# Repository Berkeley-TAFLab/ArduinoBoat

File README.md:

# Software for TAFLab Arduino Drone

Contributors: Professor Reza Alam, Evan Kuo, Arsh Khan, and Nick Bui

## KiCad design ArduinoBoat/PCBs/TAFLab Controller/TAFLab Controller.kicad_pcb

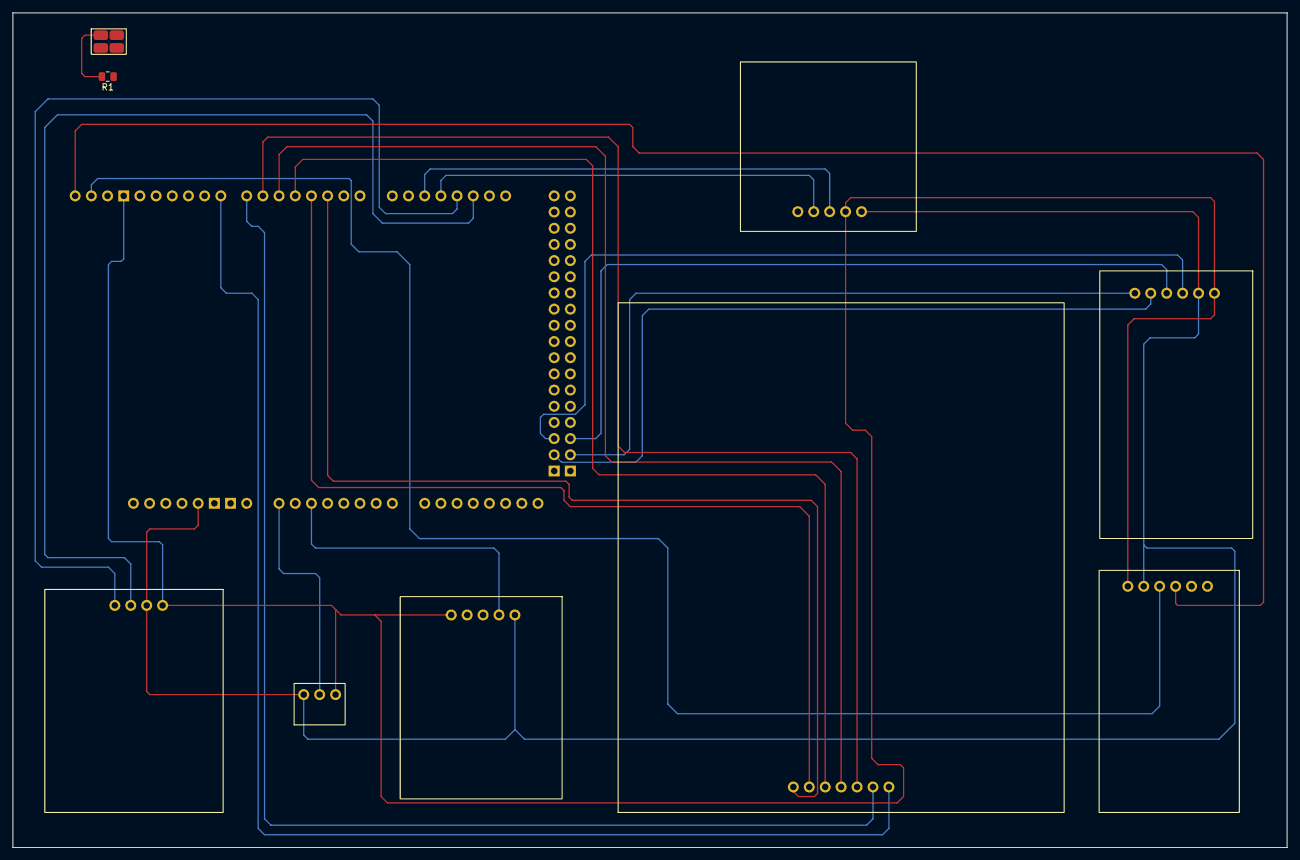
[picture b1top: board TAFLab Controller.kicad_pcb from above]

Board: 2 copper layers, 200.0 x 131.0 mm, 10 parts (0 on the bottom side), 22 nets.

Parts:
A1: Arduino_Mega2560_R3_Shield
R1: 10k; R_0805_2012Metric
RV1: R_Potentiometer; Potentiometer
U1: XBeeBreakout
U2: JoyStick
U3: Keypad
U4: HW84_DS3231_CLK_Module
U5: Micro_SD_Module
U7: GT-U7_GPS
U8: PushButton

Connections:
unnamed: A1.D2 (D2_INT0), U3.1 (ROW1)
unnamed: A1.D3 (D3_INT1), U3.2 (ROW2)
unnamed: A1.D16 (D16/TX2), U7.3 (RXD)
unnamed: A1.D17 (D17/RX2), U7.2 (TXD)
unnamed: A1.D18 (D18/TX1), U1.4 (DIN)
unnamed: A1.D19 (D19/RX1), U1.3 (DOUT)
unnamed: A1.D50 (D50_MISO), U5.3 (MISO)
unnamed: A1.D51 (D51_MOSI), U5.4 (MOSI)
unnamed: A1.D52 (D52_SCK), U5.5 (SCK)
unnamed: A1.D53 (D53_CS), U5.6 (CS)
unnamed: A1.A0, RV1.2
unnamed: A1.5V1 (5V), RV1.1, U1.2 (5V), U2.1 (VCC), U4.5 (VCC), U5.2 (VCC), U7.5 (VCC), U8.2 (VCC)
unnamed: A1.GND1 (GND), R1.1, RV1.3, U1.1 (GND), U2.5 (GND), U4.6 (GND), U5.1 (GND), U7.4 (GND)
unnamed: A1.A2, U2.2 (VERT)
unnamed: A1.D6, U3.5 (COL1)
unnamed: A1.D7, U3.6 (COL2)
unnamed: A1.D8, U3.7 (COL3)
unnamed: A1.D4, U3.3 (ROW3)
unnamed: A1.D5, U3.4 (ROW4)
unnamed: A1.SCL, U4.3 (SCL)
unnamed: A1.SDA, U4.4 (SDA)
unnamed: R1.2, U8.1 (GND)

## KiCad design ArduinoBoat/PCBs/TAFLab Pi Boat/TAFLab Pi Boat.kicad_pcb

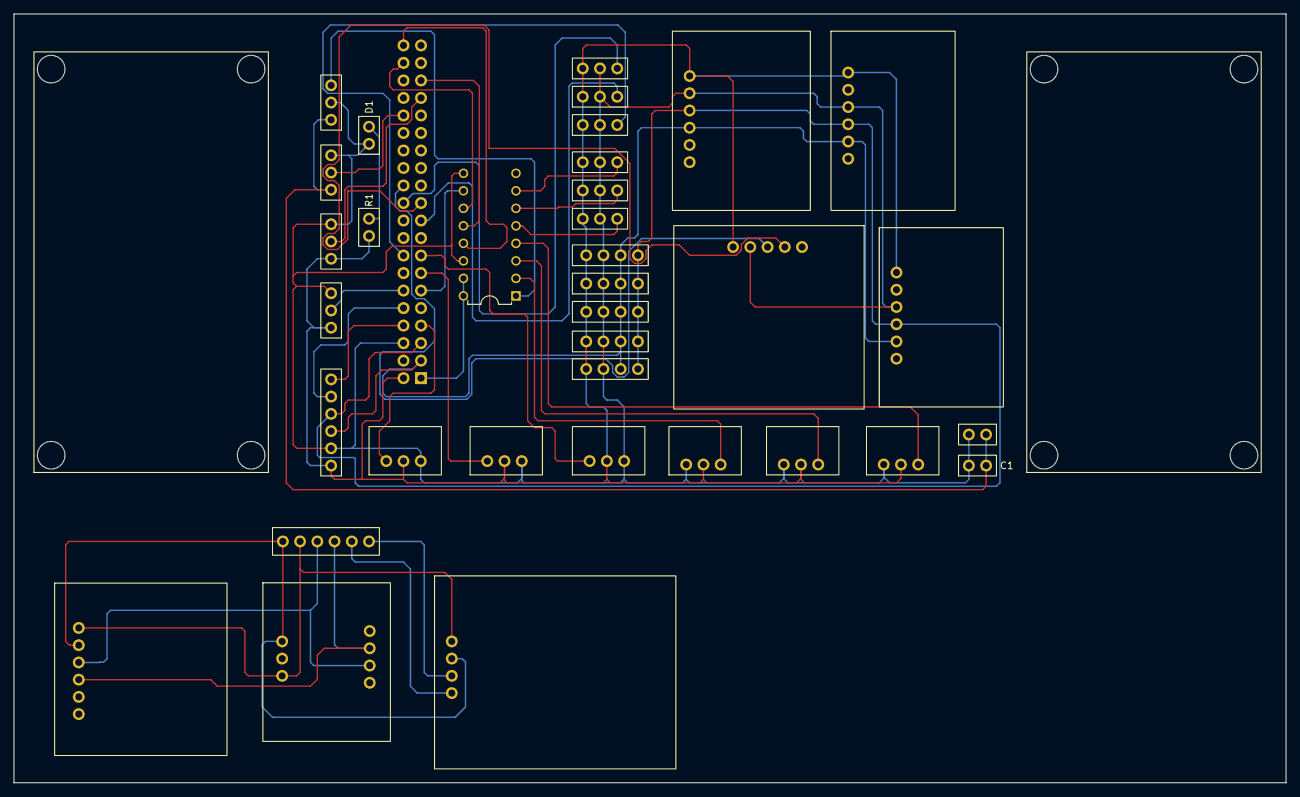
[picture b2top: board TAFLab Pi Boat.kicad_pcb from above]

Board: 2 copper layers, 184.5 x 111.5 mm, 38 parts (0 on the bottom side), 37 nets.

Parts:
C1: 10k µF; Default2Pin
D1: LED; Default2Pin
R1: 300Ω; Default2Pin
RP1: Raspberry_Pi_2_3; RaspberryPi_4
U1: AS5600_Magnetic_Encoder_Windvane
U2: BME280_PHT
U3: XBeeBreakout
U4: GT-U7_GPS
U5: LIS3MDL_Magnetometer
U6: MPU6050_IMU_Accelerometer
U7, U8, U9: DS18B20_Water_Temp_Sensor
U10, U11, U12: HW038_WaterLevelSensor
U13, U15: LM2596S-12; LM2596
U14: INA219_BatteryPowerSensor
U16, U17, U18: ActuatorConnector
U19, U20, U21, U22, U23, U24, U30: Default3Pin
U25, U26, U27, U28, U29: Default4Pin
U31: Top_Boat_PCB
U32: SailWireConnector
U33: MCP3008
U34: Default2Pin

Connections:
+3.3V: RP1.1 (+3.3V_1), U33.15 (Vref), U33.16 (Vdd)
+5V: R1.1, RP1.2 (+5V_1), U4.5 (5V), U5.1 (5V), U6.1 (5V), U7.2 (5V), U8.2 (5V), U9.2 (5V), U10.2 (5V), U11.2 (5V), U12.2 (5V), U14.1 (5V), U16.1 (5V), U17.1 (5V), U19.1 (5V), U20.1 (5V), U21.1 (5V), U22.1 (5V), U23.1 (5V), U24.1 (5V), U25.1 (5V), U26.1 (5V), U27.1 (5V), U28.1 (5V), U29.1 (5V), U32.1 (5V)
+8V: C1.2, U18.1 (8V), U30.1 (8V), U34.1 (8V)
A0: U30.3 (ANA), U33.1 (CH0)
A1: U10.1 (ANA), U33.2 (CH1)
A2: U11.1 (ANA), U33.3 (CH2)
A3: U12.1 (ANA), U33.4 (CH3)
A4: U22.3 (DIG/ANA), U33.5 (CH4)
A5: U23.3 (DIG/ANA), U33.6 (CH5)
A6: U24.3 (DIG/ANA), U33.7 (CH6)
CLK: RP1.40 (GPIO21/SPI0_SCLK1), U33.13 (CLK)
CS/SHDN: RP1.11 (GPIO_17/SPI1_CS1), U33.10 (~CS/SHDN)
D0: RP1.7 (GPIO_4/GPCLK0), U7.1 (DIG)
D1: RP1.13 (GPIO27), U8.1 (DIG)
D2: RP1.15 (GPIO_22), U9.1 (DIG)
D3: RP1.16 (GPIO_23), U19.3 (DIG/ANA)
D4: RP1.19 (GPIO_10/SPI0_MOSI), U20.3 (DIG/ANA)
D5: RP1.22 (GPIO_25), U21.3 (DIG/ANA)
DIN: RP1.38 (GPIO20/SPI0_MOSI1), U33.11 (Din)
DOUT: RP1.35 (GPIO19/SPI0_MISO1/PWM1), U33.12 (Dout)
GND: C1.1, D1.1 (K), RP1.6 (GND_1), U4.4 (GND), U5.3 (GND), U6.3 (GND), U7.3 (GND), U8.3 (GND), U9.3 (GND), U10.3 (GND), U11.3 (GND), U12.3 (GND), U14.2 (GND), U16.3 (GND), U17.3 (GND), U18.3 (GND), U19.2 (GND), U20.2 (GND), U21.2 (GND), U22.2 (GND), U23.2 (GND), U24.2 (GND), U25.2 (GND), U26.2 (GND), U27.2 (GND), U28.2 (GND), U29.2 (GND), U30.2 (GND), U32.2 (GND), U33.9 (DGND), U33.14 (AGND), U34.2 (GND)
unnamed: D1.2 (A), R1.2
unnamed: U1.1 (3V/5V), U2.2 (3V/5V), U3.2 (5V), U31.1 (5V)
unnamed: U1.3 (GND), U2.1 (GND), U3.1 (GND), U31.2 (GND)
unnamed: U1.5 (SCL), U2.4 (SCL), U31.4 (SCL)
unnamed: U1.6 (SDA), U2.3 (SDA), U31.3 (SDA)
unnamed: U3.4 (RX), U31.5 (RX)
unnamed: U3.3 (TX), U31.6 (TX)
PWM0: RP1.32 (GPIO12/PWM0), U18.2 (DIG)
PWM1: RP1.33 (GPIO13/PWM1), U17.2 (DIG)
PWM2: RP1.12 (GPIO_18/PWM0/SPI1_CS0), U16.2 (DIG)
RX0: RP1.8 (GPIO_14/[UART]_TXD0), U32.6 (RX)
RX1: RP1.24 (GPIO_8/SPI0_CE1_N), U4.3 (RX)
SCL: RP1.5 (GPIO_3/[I2C]_SCL), U5.4 (SCL), U6.4 (SCL), U14.3 (SCL), U25.4 (SCL), U26.4 (SCL), U27.4 (SCL), U28.4 (SCL), U29.4 (SCL), U32.4 (SCL)
SDA: RP1.3 (GPIO_2/[I2C]_SDA), U5.5 (SDA), U6.5 (SDA), U14.4 (SDA), U25.3 (SDA), U26.3 (SDA), U27.3 (SDA), U28.3 (SDA), U29.3 (SDA), U32.3 (SDA)
TX0: RP1.10 (GPIO_15/[UART]_RXD0), U32.5 (TX)
TX1: RP1.21 (GPIO_9/SPI0_MISO), U4.2 (TX)

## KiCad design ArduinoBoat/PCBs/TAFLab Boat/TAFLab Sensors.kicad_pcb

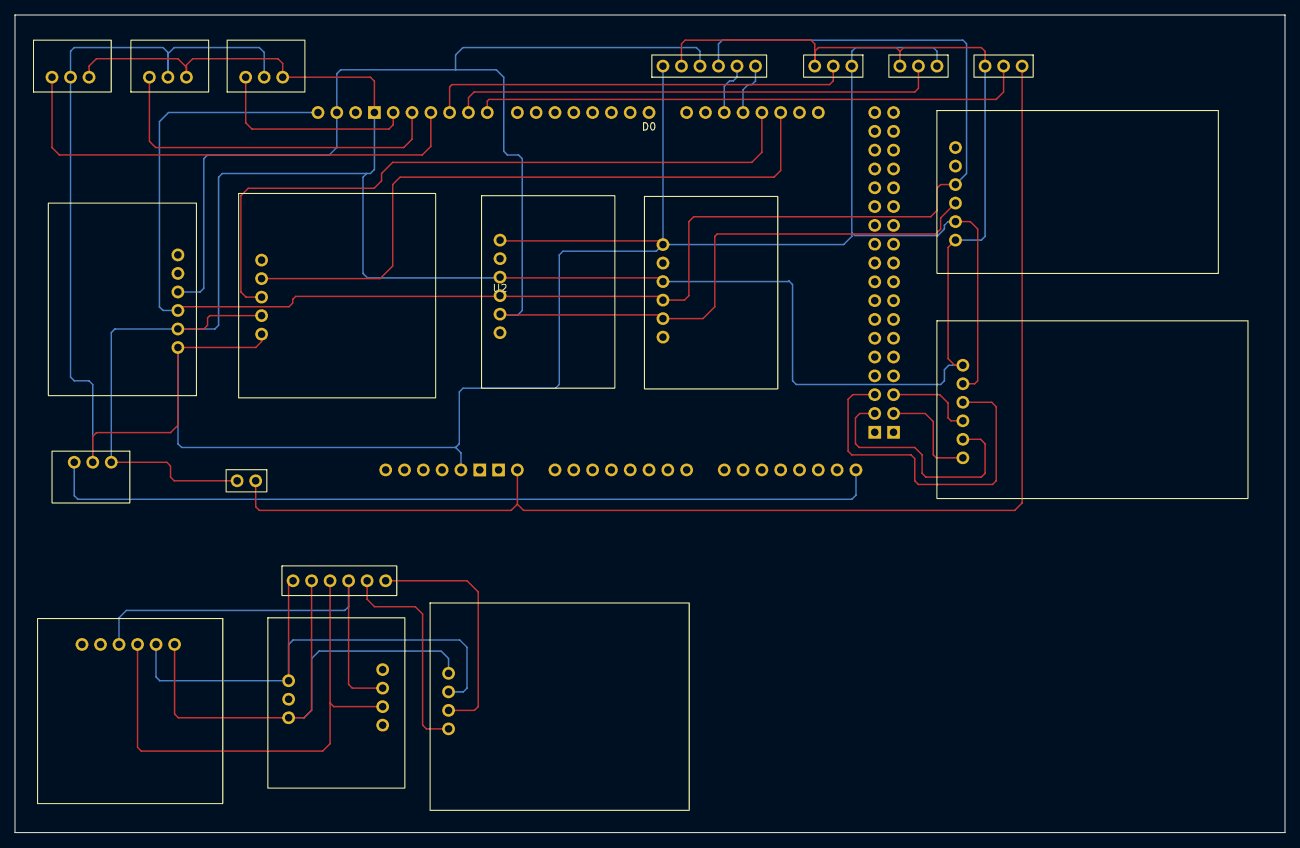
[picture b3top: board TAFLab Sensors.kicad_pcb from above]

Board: 2 copper layers, 171.5 x 110.4 mm, 20 parts (0 on the bottom side), 27 nets.

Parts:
A1: Arduino_Mega2560_R3_Shield
U2: LIS3MDL_Magnometer
U3: MPU6050_IMU_Accelerometer
U4: INA219_BatteryPowerSensor
U5: AS5600_Magnetic_Encoder_Windvane
U6: BME280_PHT
U7: GT-U7_GPS
U8: XBeeBreakout
U9: HW038_WaterLevelSensor
U10, U19, U20: DS18B20_Water_Temp_Sensor
U11: Micro_SD_Module
U12: Top_Boat_PCB
U13: HW84_DS3231_CLK_Module
U14, U16, U17: ActuatorConnector
U15: VinArduinoConnector
U18: SailWireConnector

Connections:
unnamed: A1.D16 (D16/TX2), U18.5 (Tx)
unnamed: A1.D17 (D17/RX2), U18.6 (Rx)
unnamed: A1.D18 (D18/TX1), U7.3 (RXD)
unnamed: A1.D19 (D19/RX1), U7.2 (TXD)
unnamed: A1.D50 (D50_MISO), U11.3 (MISO)
unnamed: A1.D51 (D51_MOSI), U11.4 (MOSI)
unnamed: A1.D52 (D52_SCK), U11.5 (SCK)
unnamed: A1.D53 (D53_CS), U11.6 (CS)
unnamed: A1.D8, U16.2 (D8)
unnamed: A1.D9, U17.2 (D9)
unnamed: A1.D10, U14.2 (D10)
unnamed: A1.VIN, U15.1 (Vin), U16.1 (8V)
unnamed: U5.3 (GND), U6.1 (GND), U8.1 (GND), U12.2 (GND)
unnamed: U5.5 (SCL), U6.4 (SCL), U12.4 (SCL)
unnamed: U5.6 (SDA), U6.3 (SDA), U12.3 (SDA)
unnamed: U5.1 (VCC), U6.2 (3v3), U8.2 (5V), U12.1 (VCC)
unnamed: U8.4 (DIN), U12.5 (Rx)
unnamed: U8.3 (DOUT), U12.6 (Tx)
unnamed: A1.A15, U9.1 (DATA)
unnamed: A1.D11, U10.1 (DATA)
unnamed: A1.GND1 (GND), U2.3 (GND), U3.3 (GND), U4.2 (GND), U7.4 (GND), U9.3 (GND), U10.3 (GND), U13.6 (GND), U15.2 (GND), U18.2 (GND), U19.3 (GND), U20.3 (GND)
unnamed: A1.5V1 (5V), U2.1 (Vin), U3.1 (Vin), U4.1 (VCC), U7.5 (VCC), U9.2 (Vin), U10.2 (Vin), U11.2 (VCC), U13.5 (VCC), U14.1 (5V), U17.1 (5V), U18.1 (VCC), U19.2 (Vin), U20.2 (Vin)
unnamed: U11.1 (GND), U14.3 (GND), U16.3 (GND), U17.3 (GND)
unnamed: A1.SCL, U2.4 (SCL), U3.4 (SCL), U4.3 (SCL), U13.3 (SCL), U18.4 (SCL)
unnamed: A1.SDA, U2.5 (SDA), U3.5 (SDA), U4.4 (SDA), U13.4 (SDA), U18.3 (SDA)
unnamed: A1.D13, U19.1 (DATA)
unnamed: A1.D12, U20.1 (DATA)

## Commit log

2024-10-30 Adding what I have
2024-10-30 Renaming folder
2024-11-13 Component Libs moved into run file
2024-11-14 11/13/2024
2024-11-14 Proto G
2024-11-19 I Calibration
2024-11-19 Prototype I Calibration Uploaded
2024-11-19 Calibration
2024-11-19 Need to fix windvane
2024-11-21 Added PCBs
2024-11-21 Removing unnecessary files from PCB
2024-11-21 Update PCB before review and order w/ Arsh
2024-12-02 PCB edits
2024-12-02 PCB changes
2025-02-13 All files
2025-02-13 test commit
2025-03-06 Initial STM32 project setup
